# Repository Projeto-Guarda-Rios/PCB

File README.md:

# Guarda-Rios PCB Repository

This repository contains all PCB design files for the **Guarda-Rios Project** — an open-source, low-cost, low-power water quality monitoring system. Multiple stations are deployed along a river so that parameter spikes between adjacent stations reveal precisely where pollution enters the waterway.

The system has two PCBs:

| Board | Role | Placement |
|---|---|---|
| **AquaNode PCB** | Submerged sensor node — reads water parameters and transmits them over RS-485 | Below waterline |
| **Main PCB (PGR)** | Station hub — receives RS-485 data, manages power (solar + 18650 Li-ion), and sends data to the cloud via NB-IoT | Above waterline |

> GitHub organisation: [github.com/Projeto-Guarda-Rios](https://github.com/Projeto-Guarda-Rios)
> Project site: [guarda-rios.pt](https://guarda-rios.pt) · Data portal: [data.guarda-rios.pt](https://data.guarda-rios.pt)

---

## Directory Structure

```
PCB/
├── AquaNode - PCB/          # AquaNode submerged sensor node
├── PGR - PCB/               # Main Station PCB
├── Datasheets/              # Component datasheets
├── Resources/               # Logos, SVGs, and images (silkscreen assets)
└── LICENSE
```

---

## AquaNode - PCB

The AquaNode is the submerged node of each station. It is built around an **STM32L053R8** microcontroller (ultra-low-power) and integrates a DS18B20 water temperature sensor (1-Wire) and a DFRobot SEN0554 turbidity sensor. Readings are encoded into the custom Guarda-Rios protocol and transmitted to the Main PCB over RS-485.

```
AquaNode - PCB/
├── Renders/                              # PNG renders of the current board
│   ├── AquaNode - PCB.png               #   Top-side render
│   └── AquaNode - PCB - 2.png           #   Bottom-side / alternate angle render
│
├── AquaNode - PCB.step                  # STEP model of the assembled board
├── AquaNode - PCB - Render.step         # STEP model used for rendering
├── AquaNode - PCB.stl                   # STL mesh of the board
│
└── AquaNode - PCB/                      # KiCAD project (current version)
    ├── AquaNode - PCB.kicad_pro         #   KiCAD project file  ← open this in KiCAD
    ├── AquaNode - PCB.kicad_pcb         #   PCB layout
    ├── AquaNode - PCB.kicad_sch         #   Schematic
    ├── footprints/                      #   Custom footprint library
    ├── symbols/                         #   Custom symbol library
    └── production/                      # Production files (PCBA) — current version
        ├── -v2.0.zip                    #   Gerbers + drill files (upload to JLCPCB)
        ├── -v2.0_bom.csv               #   Bill of Materials
        ├── -v2.0_positions.csv         #   Component placement (pick & place)
        ├── -v2.0_designators.csv       #   Designator mapping
        ├── netlist.ipc                  #   IPC netlist
        └── backups/                     #   Auto-generated production backups
```

**Key files:**
- Edit the PCB: `AquaNode - PCB/AquaNode - PCB/AquaNode - PCB.kicad_pro`
- Order the board: `AquaNode - PCB/AquaNode - PCB/production/-v2.0.zip`
- BOM for assembly: `AquaNode - PCB/AquaNode - PCB/production/-v2.0_bom.csv`
- Positions for assembly: `AquaNode - PCB/AquaNode - PCB/production/-v2.0_positions.csv`

---

## PGR - PCB

The Main PCB (PGR) is the above-water hub of each station. It is built around an **ESP32-WROOM-32D** and includes an RS-485 receiver, NB-IoT modem, BMS (battery management system), 18650 Li-ion charger, and solar charger — making each station fully self-sufficient in the field.

```
PGR - PCB/
├── Renders/                              # PNG renders of the current board
│   ├── PGR.png                          #   Top-side render
│   └── PGR - 2.png                      #   Bottom-side / alternate angle render
│
├── PGR.step                             # STEP model of the assembled board
├── PGR-Solder.step                      # STEP model showing solder joints
├── PGR.3mf                             # 3MF model (for 3D printing / Fusion 360)
│
├── PGR - PCB - v1.0-v4.0.zip           # Archived KiCAD projects (versions 1.0 – 4.0)
├── PGR - PCB - v5.0.zip                # Archived KiCAD project (version 5.0)
│
├── gerbers/                             # Gerber archives for previous board versions
│   ├── PGR-gerbers-v1.0.zip
│   ├── PGR-gerbers-v2.0.zip
│   ├── PGR-gerbers-v3.0.zip
│   ├── PGR-gerbers-v3.1.zip
│   ├── PGR-gerbers-v4.0.zip
│   ├── PGR-gerbers.zip                  #   (legacy export)
│   ├── PGR-F_Paste.zip                  #   Front paste layer export
│   └── PGR-PTH.zip                      #   PTH drill file export
│
└── PGR - PCB/                           # KiCAD project (current version)
    ├── PGR.kicad_pro                    #   KiCAD project file  ← open this in KiCAD
    ├── PGR.kicad_pcb                    #   PCB layout
    ├── PGR.kicad_sch                    #   Schematic
    ├── PGR-Library.kicad_sym           #   Custom symbol library
    ├── PGR-FootPrints.pretty/          #   Custom footprint library
    ├── footprints/                      #   Additional footprints
    ├── symbols/                         #   Additional symbols
    └── production/                      # Production files (PCBA) — current versions
        ├── PGR_PCB_v5.1.zip            #   Gerbers + drill files — latest (upload to JLCPCB)
        ├── PGR_PCB_v5.1_bom.csv        #   Bill of Materials — latest
        ├── PGR_PCB_v5.1_positions.csv  #   Component placement — latest
        ├── PGR_PCB_v5.1_designators.csv
        ├── PGR_PCB_v5.0.zip            #   Gerbers + drill files — v5.0
        ├── PGR_PCB_v5.0_bom.csv        #   Bill of Materials — v5.0
        ├── PGR_PCB_v5.0_positions.csv
        ├── PGR_PCB_v5.0_designators.csv
        ├── bom-JLCPCB Assembly Order.xls  # JLCPCB-formatted BOM for online ordering
        ├── bom.csv
        ├── designators.csv
        ├── positions.csv
        ├── netlist.ipc
        └── backups/                    # Auto-generated production backups
```

**Key files:**
- Edit the PCB: `PGR - PCB/PGR - PCB/PGR.kicad_pro`
- Order the board (latest): `PGR - PCB/PGR - PCB/production/PGR_PCB_v5.1.zip`
- BOM for assembly (latest): `PGR - PCB/PGR - PCB/production/PGR_PCB_v5.1_bom.csv`
- Positions for assembly (latest): `PGR - PCB/PGR - PCB/production/PGR_PCB_v5.1_positions.csv`
- Previous version gerbers: `PGR - PCB/gerbers/`

> Note: There are no current production files inside `PGR - PCB/gerbers/` — that directory holds archives of older board revisions only. Current production files are inside `PGR - PCB/PGR - PCB/production/`.

---

## Datasheets

Reference datasheets for ICs and components used across both PCBs.

```
Datasheets/
├── STM32L053C6.PDF                       # AquaNode MCU — STM32L053 datasheet
├── an4467-getting-started-with-stm32l0xx-hardware-development-stmicroelectronics.pdf
│                                         # STM32L0 hardware development guide (ST AppNote AN4467)
└── st485eb.pdf                           # ST485EB RS-485 transceiver (used on AquaNode)
```

---

## Resources

Images, SVGs, and logos used in PCB silkscreen layers or project documentation.

```
Resources/
├── guarda_rios_logo.svg / .png          # Official Guarda-Rios project logo
├── dwtLogo.svg                          # Designer logo
├── MIT_license_logo.svg / .png         # MIT license badge
├── open_source_logo.svg                 # Open-source hardware logo
├── open-source-hardware6230.logowik.com.webp
├── logo-colegio-ribadouro.png           # School/institution logo
│
├── AquaNodeBack.svg                     # AquaNode back silkscreen artwork
├── AquaNodeBack - Sem Logo.svg          # AquaNode back silkscreen (no logo variant)
├── BackSilkScreen.svg                   # Generic back silkscreen asset
│
├── AquaNode_v2_image_top.png            # AquaNode v2 board image — top
├── AquaNode_v2_image_bottom.png         # AquaNode v2 board image — bottom
├── PGR_v5.1_image_top.png              # PGR v5.1 board image — top
├── PGR_v5.1_image_bottom.png           # PGR v5.1 board image — bottom
│
└── Gemini_Generated_Image_iya1lhiya1lhiya1.png   # AI-generated concept image
```

---

## Hardware Summary

| Parameter | AquaNode PCB | Main PCB (PGR) |
|---|---|---|
| MCU | STM32L053R8 | ESP32-WROOM-32D |
| Sensors | DS18B20 (temp), DFRobot SEN0554 (turbidity) | — |
| Communication | RS-485 out (custom protocol) | RS-485 in · NB-IoT out |
| Power | From Main PCB via RS-485 cable | Solar + 18650 Li-ion (BMS + charger on-board) |
| Placement | Submerged | Above waterline |
| CAD tool | KiCAD | KiCAD |

---

## License

This project is fully open-source. See [`LICENSE`](LICENSE) for details.

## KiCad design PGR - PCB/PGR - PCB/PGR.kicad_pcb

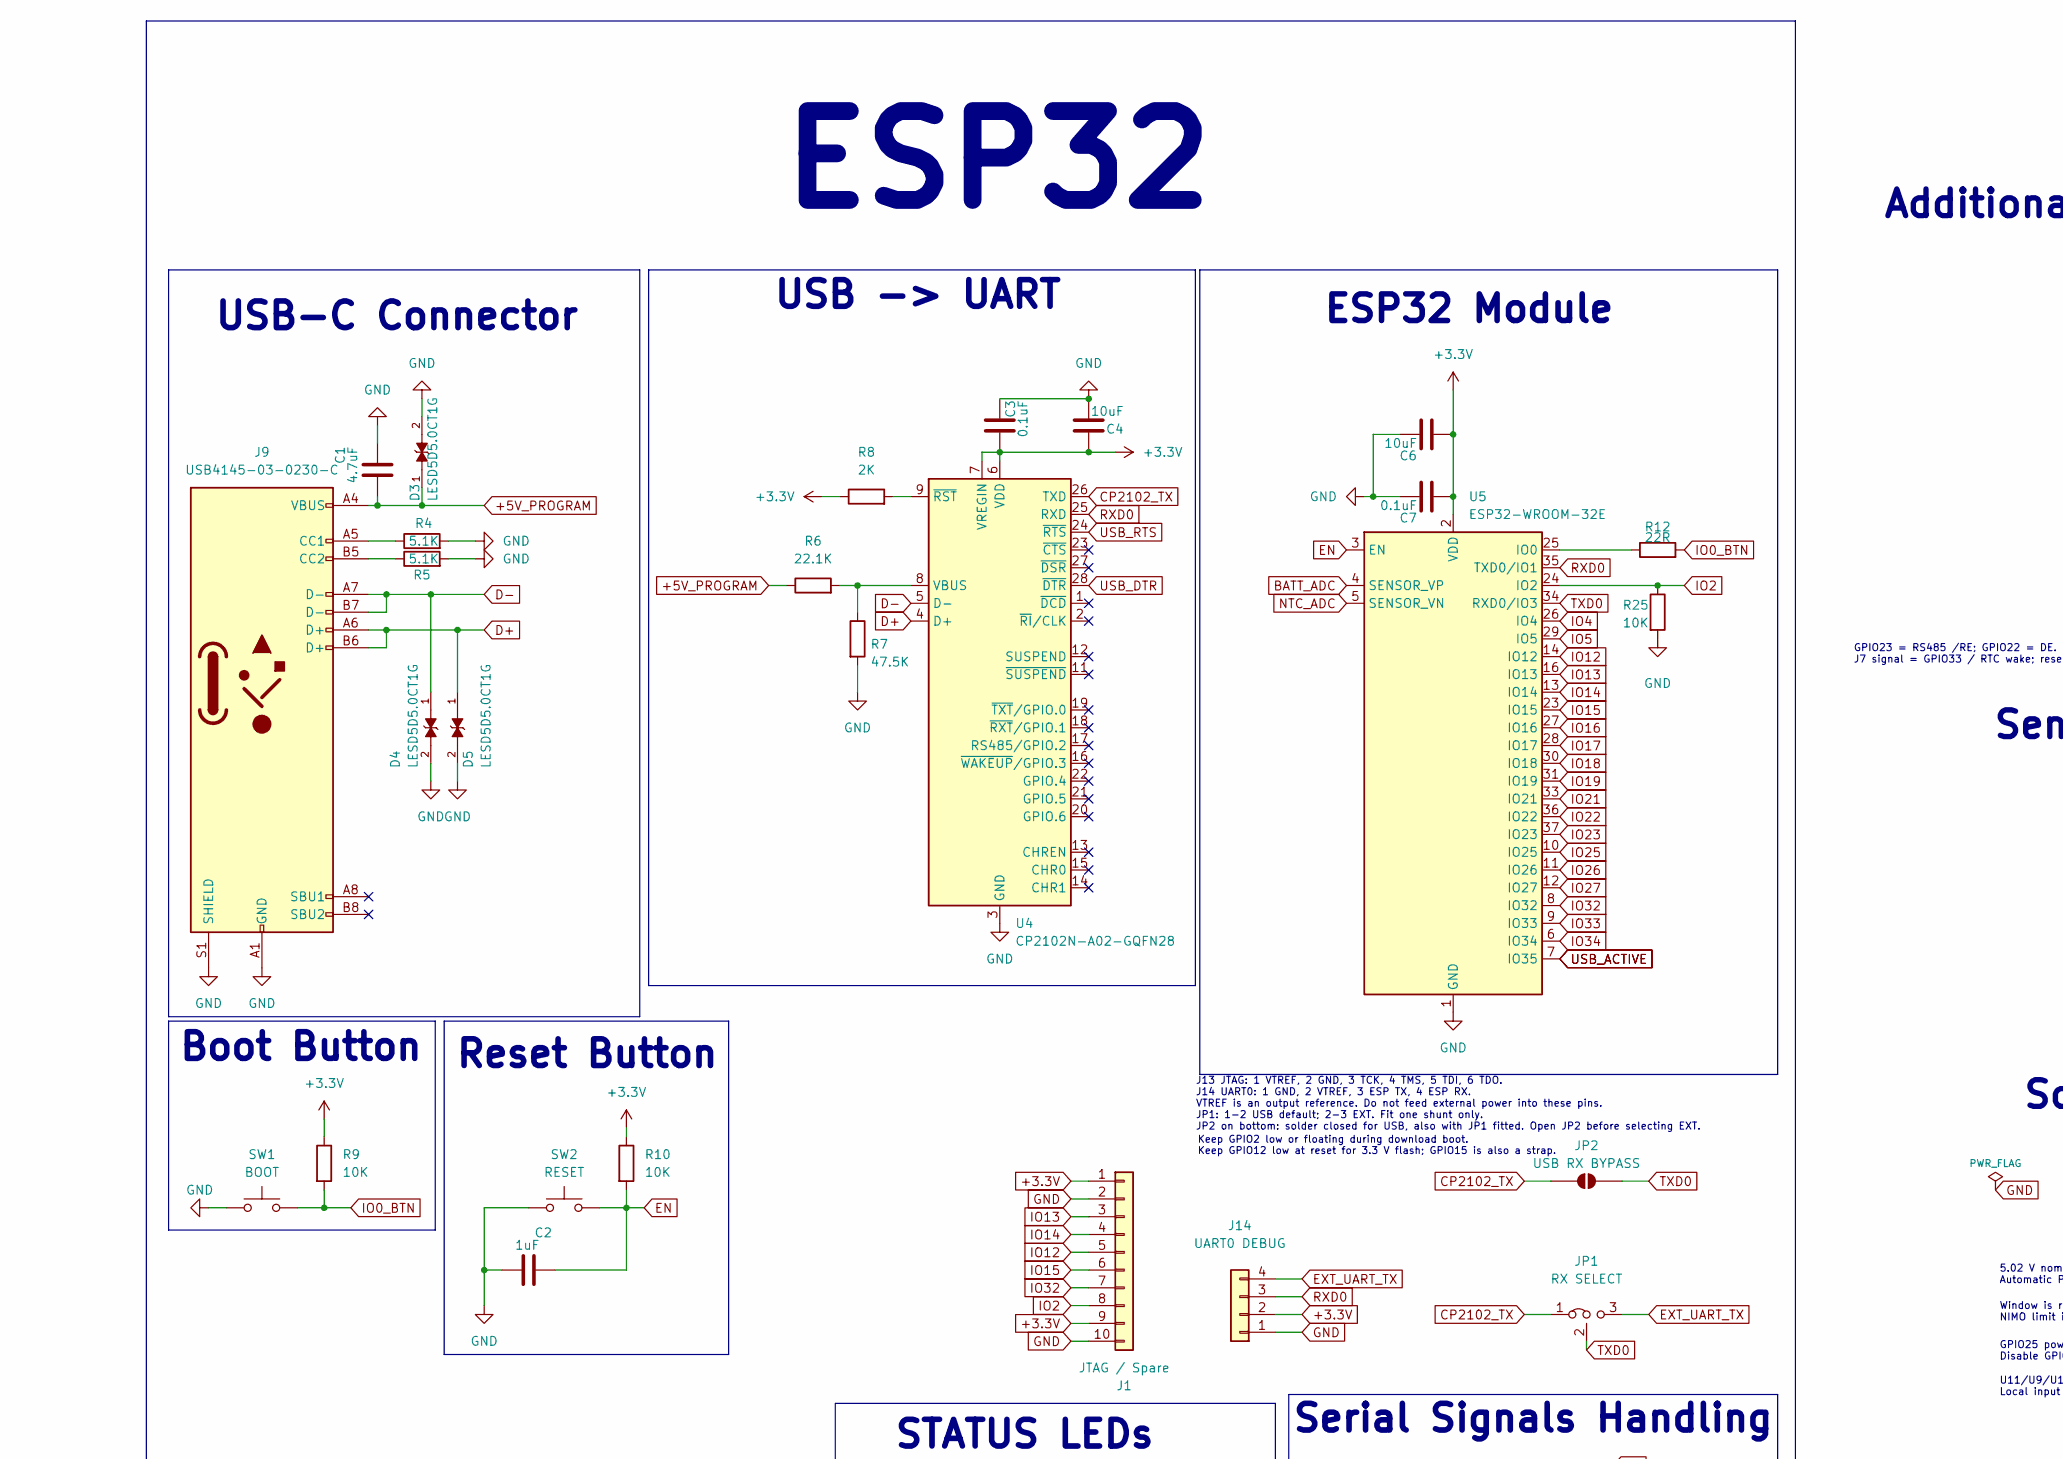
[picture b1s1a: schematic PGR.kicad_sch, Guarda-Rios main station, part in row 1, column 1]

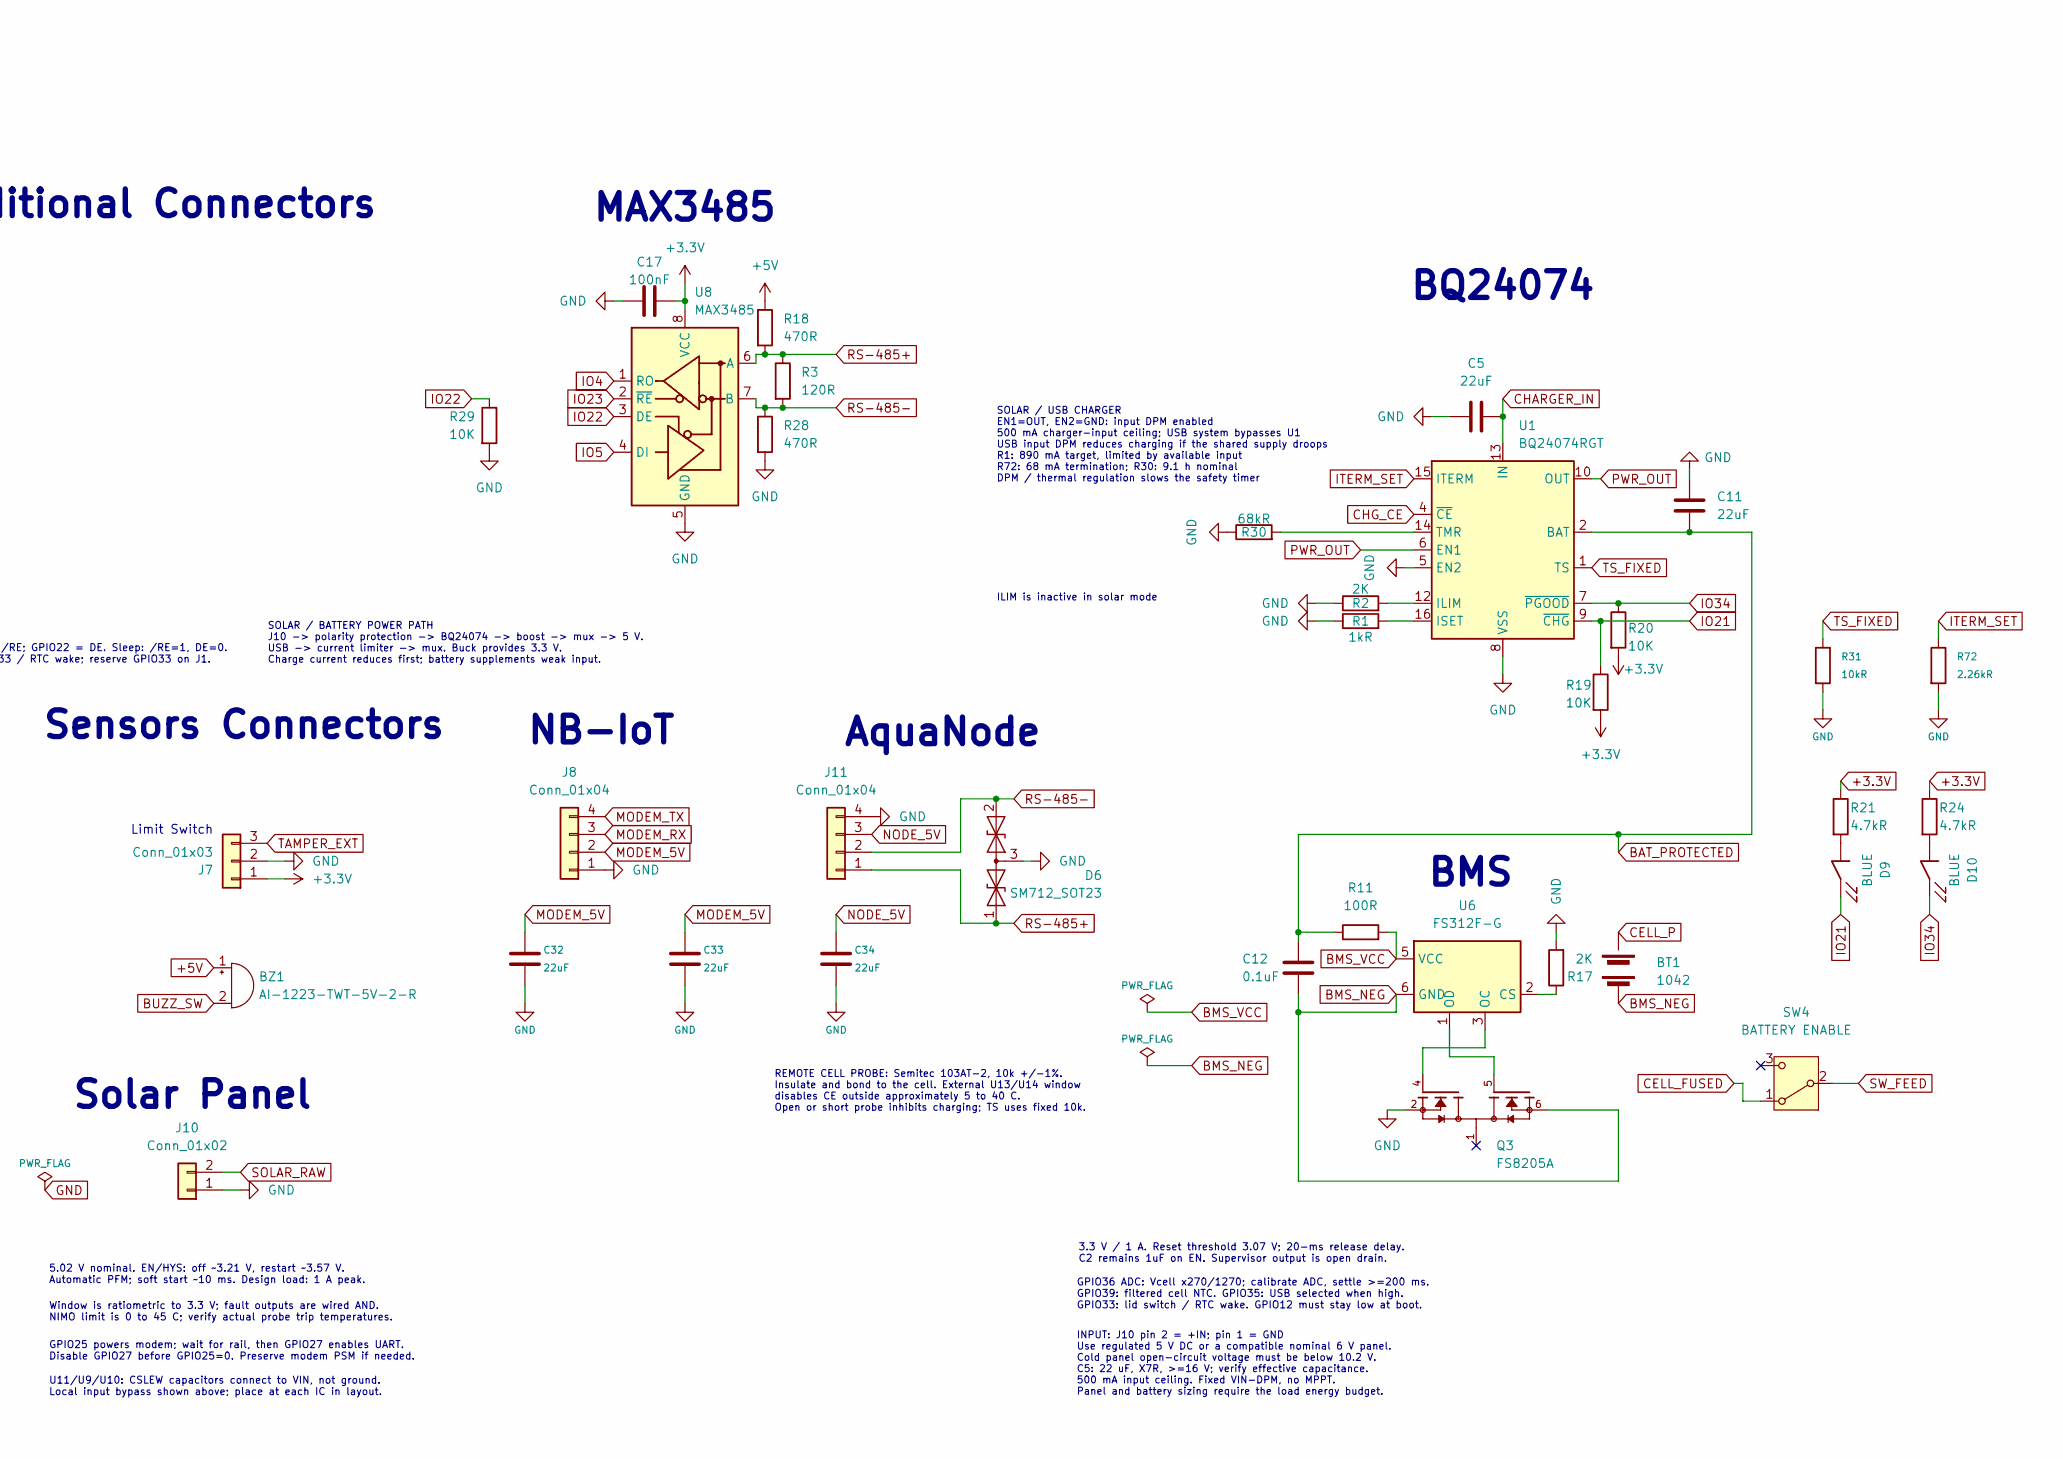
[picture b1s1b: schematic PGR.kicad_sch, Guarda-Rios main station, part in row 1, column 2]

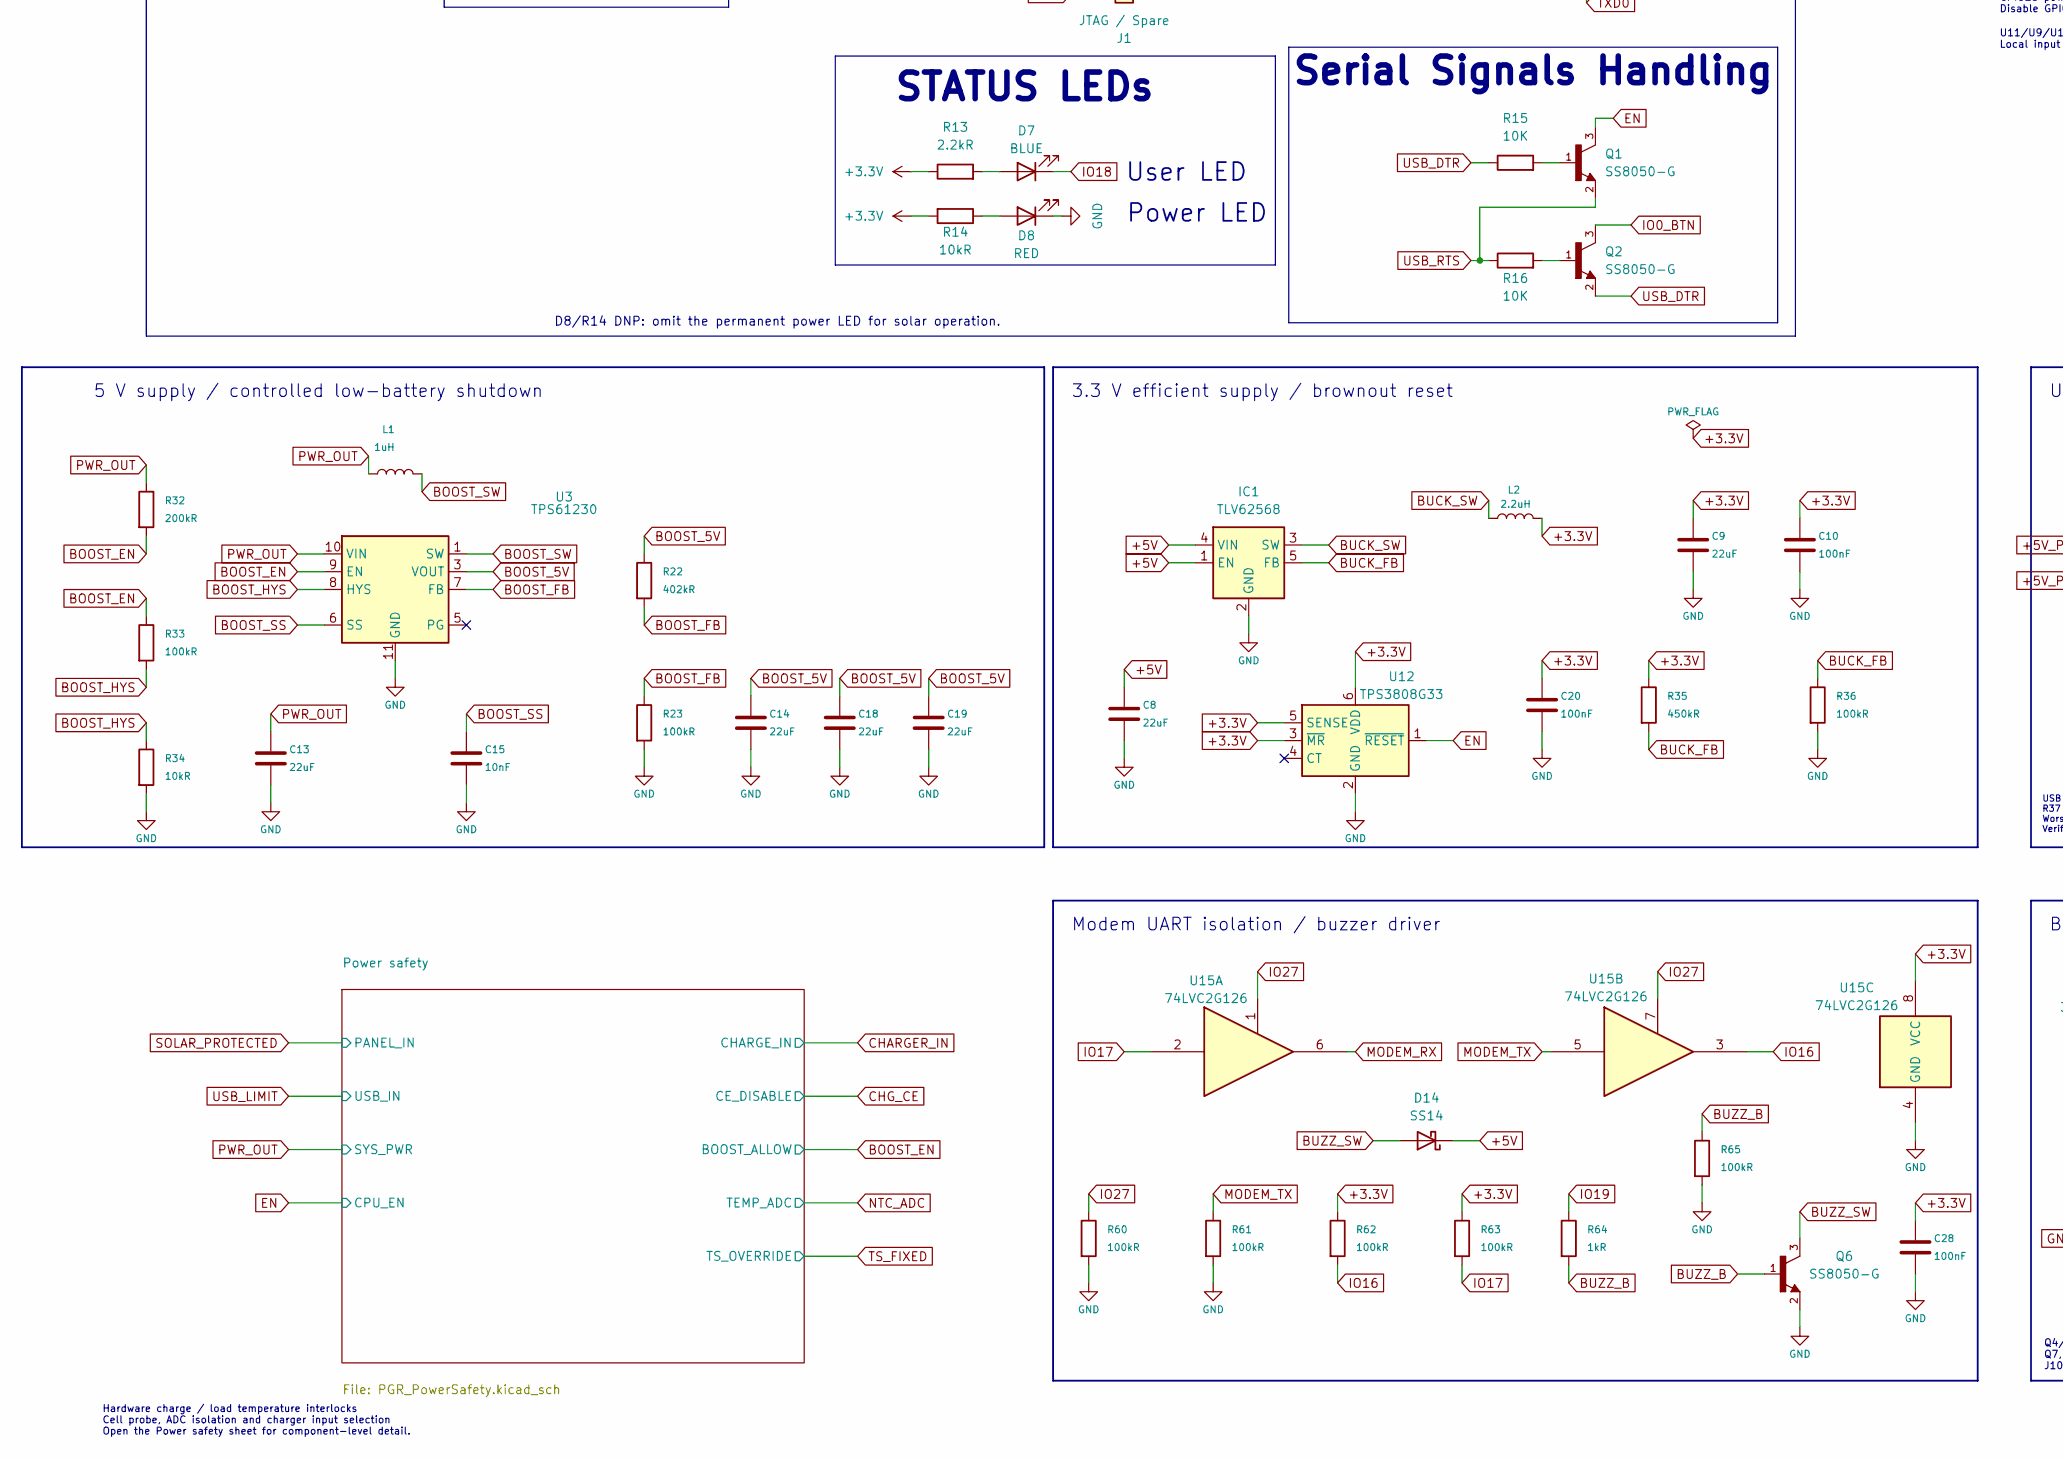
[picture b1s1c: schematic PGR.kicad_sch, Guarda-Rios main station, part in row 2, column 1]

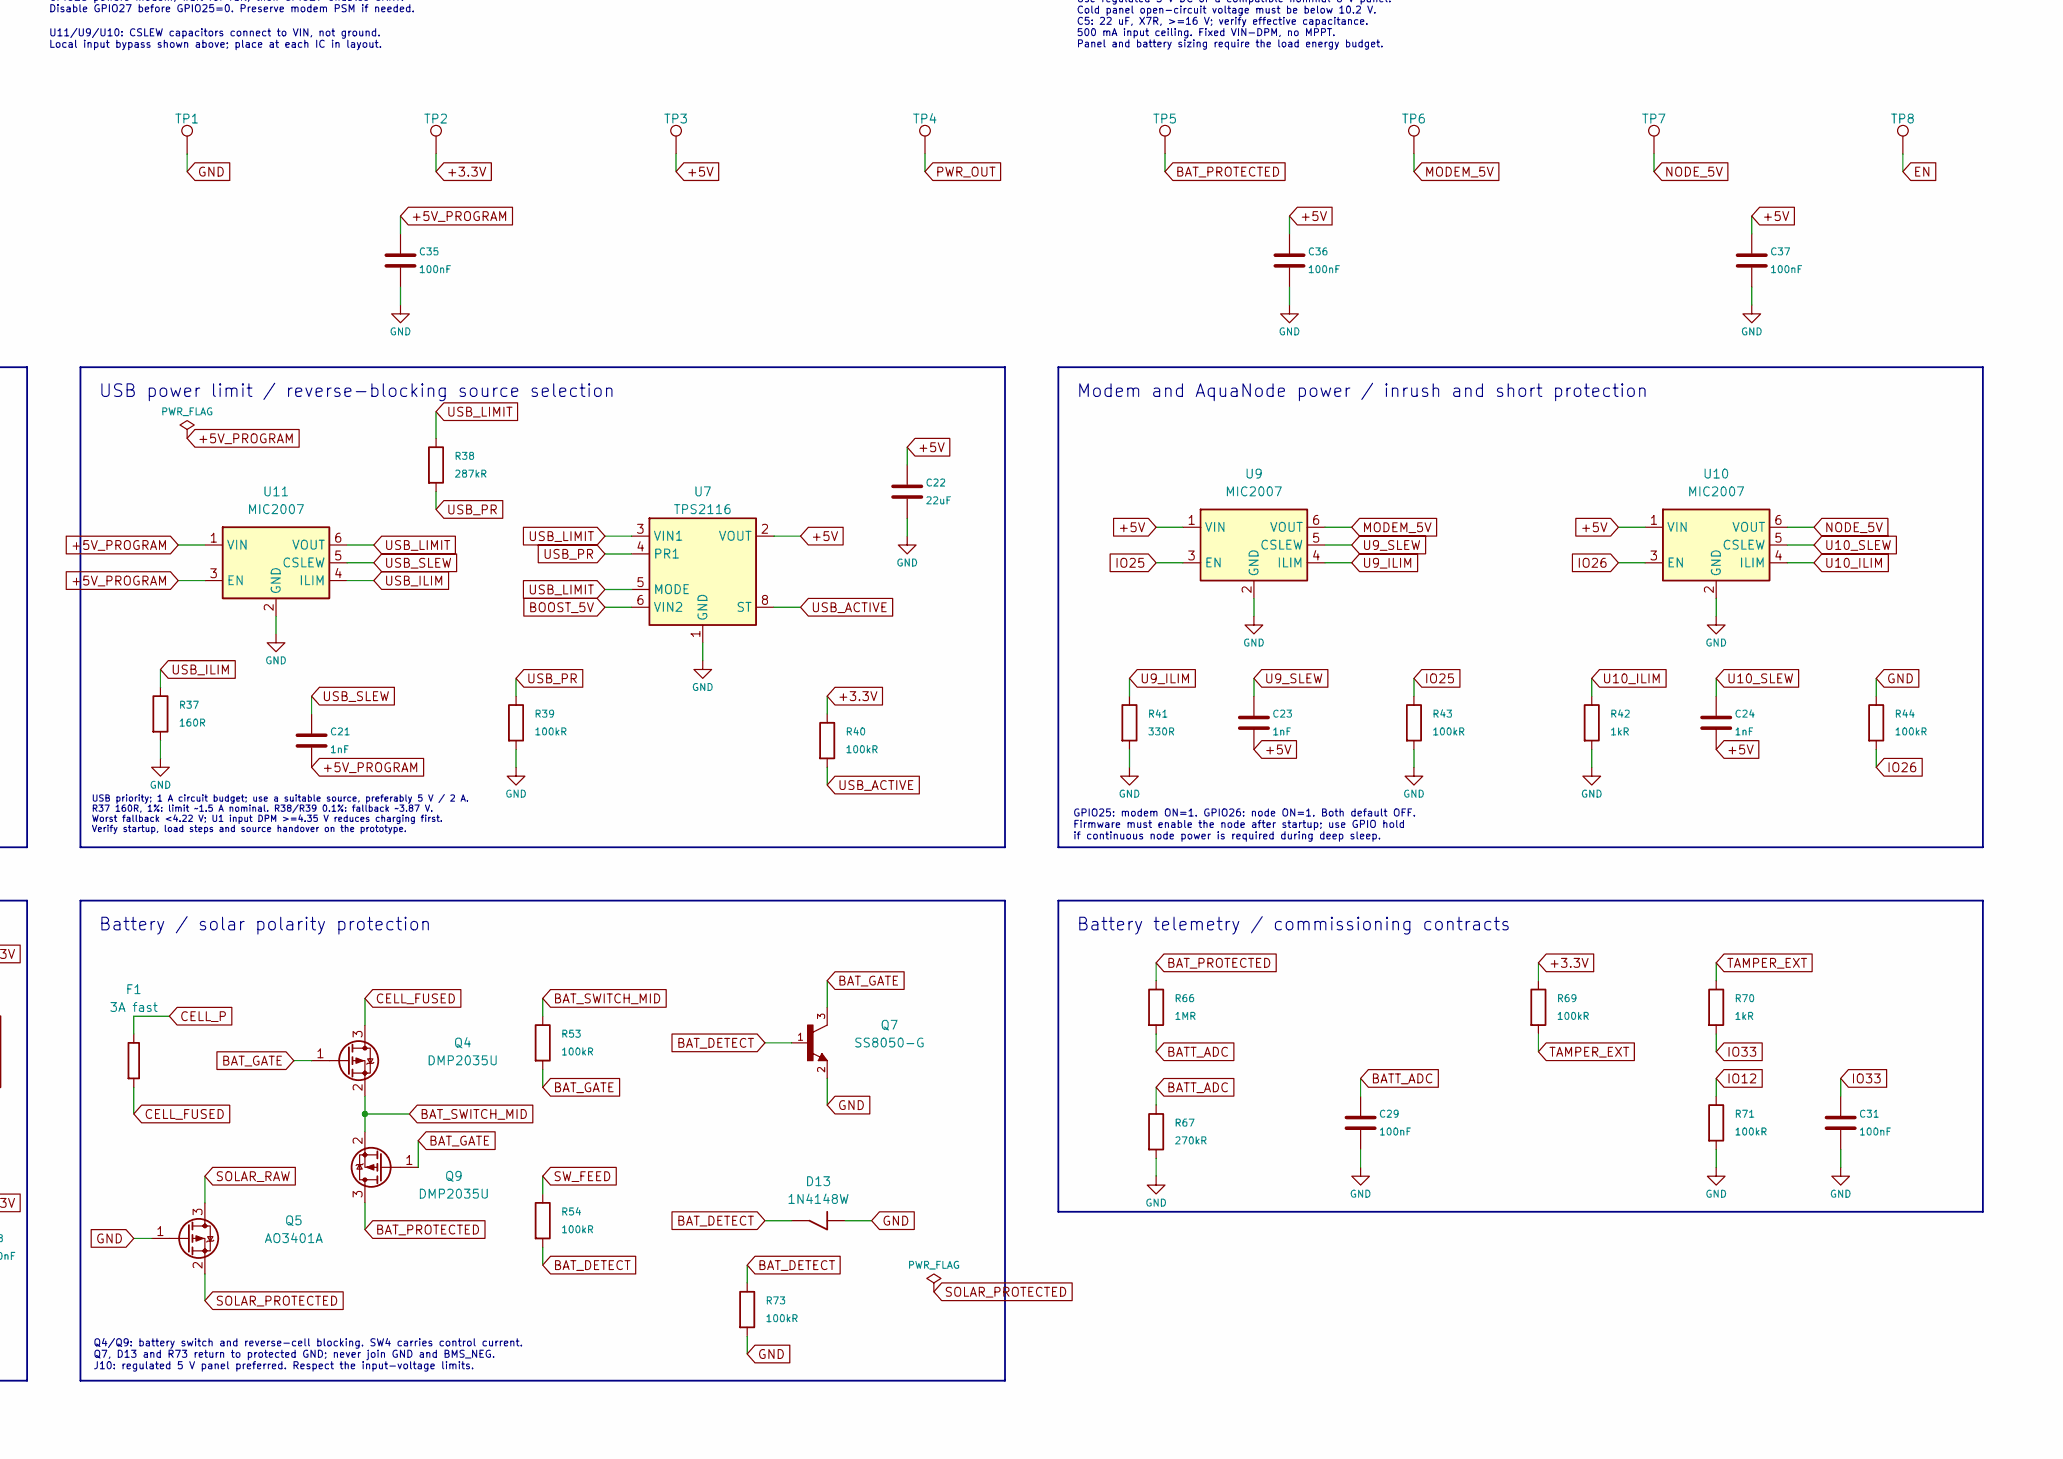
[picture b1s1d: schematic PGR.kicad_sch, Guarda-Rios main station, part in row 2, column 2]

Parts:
BT1: 1042; BatteryHolder_Keystone_1042_1x18650; MPN 1042; LCSC C5249310
BZ1: AI-1223-TWT-5V-2-R; Buzzer_12x9.5RM7.6; Rating 5V active magnetic indicator, 30mA max;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; MPN AI-1223-TWT-5V-2-R
C1: 4.7uF; C_0805_2012Metric; Rating >=10V X7R; effective >=1uF at 5V
C2: 1uF; C_0603_1608Metric
C3, C7, C12: 0.1uF; C_0603_1608Metric
C4, C6: 10uF; C_0805_2012Metric
C5, C11: 22uF; C_1210_3225Metric; Rating 16V X7R +/-20%; verify effective C >=4.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; MPN C3225X7R1C226M250AC
C8, C9, C13, C14, C18, C19, C22: 22uF; C_1210_3225Metric; Rating 22uF 16V X7R +/-20%; 1210; DC bias eval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; MPN C3225X7R1C226M250AC
C10, C17, C20, C28, C29, C31, C35, C36, C37: 100nF; C_0603_1608Metric
C15: 10nF; C_0603_1608Metric
C21, C23, C24: 1nF; C_0603_1608Metric
C32, C33, C34: 22uF; C_1210_3225Metric; Rating 16V X7R +/-20%; MPN C3225X7R1C226M250AC
D3, D4, D5: LESD5D5.0CT1G; TVS_LESD5D5.0CT1G; PARTREV O
D6: SM712_SOT23; SOT-23
D7: BLUE; LED_0603_1608Metric
D8: RED; LED_0603_1608Metric
D9: BLUE; LED_0603_1608Metric_PGR_D9
D10: BLUE; LED_0603_1608Metric_PGR_D10
D13: 1N4148W; D_SOD-123; MPN 1N4148W-7-F
D14: SS14; D_SMA; MPN SS14
F1: 3A fast; Fuse_Littelfuse-NANO2-451_453_PGR_F1; Rating 3A very fast; 300A breaking at 32VDC; MPN 0451003.MRL
IC1: TLV62568; SOT-23-5; MPN TLV62568DBVR
J1: JTAG / Spare; PinHeader_1x10_P2.54mm_Vertical
J7: Conn_01x03; JST_XH_B3B-XH-A_1x03_P2.50mm_Vertical
J8: Conn_01x04; JST_XH_B4B-XH-A_1x04_P2.50mm_Vertical
J9: USB4145-03-0230-C; USB_C_GCT_USB4145_03_0230_C_Vertical; MPN USB4145-03-0230-C; LCSC C5291559
J10: Conn_01x02; JST_XH_B2B-XH-A_1x02_P2.50mm_Vertical
J11: Conn_01x04; JST_XH_B4B-XH-A_1x04_P2.50mm_Vertical_PGR_J11
J14: UART0 DEBUG; PinHeader_1x04_P2.54mm_Vertical
JP1: RX SELECT; PinHeader_1x03_P2.54mm_Vertical; MPN M20-9990345
JP2: USB RX BYPASS; SolderJumper-2_P1.3mm_Open_Pad1.0x1.5mm
L1: 1uH; L_Coilcraft_XAL4020-XXX; MPN XAL4020-102MEC
L2: 2.2uH; L_Coilcraft_XAL4020-XXX; MPN XAL4020-222MEC
Q1: SS8050-G; TRANS_SS8050-G_PGR_Q1; PARTREV A
Q2: SS8050-G; TRANS_SS8050-G_PGR_Q2; PARTREV A
Q3: FS8205A; SOP65P640X120-8N; PARTREV 1.7
Q4, Q9: DMP2035U; SOT-23; MPN DMP2035U-7
Q5: AO3401A; SOT-23; MPN AO3401A
Q6, Q7: SS8050-G; TRANS_SS8050-G; PARTREV A
R1, R42, R64, R70: 1kR; R_0603_1608Metric
R2, R8, R17: 2K; R_0603_1608Metric
R3: 120R; R_0603_1608Metric
R4, R5: 5.1K; R_0603_1608Metric
R6: 22.1K; R_0603_1608Metric
R7: 47.5K; R_0603_1608Metric
R9, R10, R15, R16, R19, R20, R25, R29: 10K; R_0603_1608Metric
R11: 100R; R_0603_1608Metric
R12: 22R; R_0603_1608Metric
R13: 2.2kR; R_0603_1608Metric
R14, R31: 10kR; R_0603_1608Metric
R18, R28: 470R; R_0603_1608Metric; Tolerance 1%
R21, R24: 4.7kR; R_0603_1608Metric
R22: 402kR; R_0603_1608Metric; Tolerance 0.1%; MPN RT0603BRD07402KL
R23: 100kR; R_0603_1608Metric; Tolerance 0.1%; MPN RT0603BRD07100KL
R30: 68kR; R_0603_1608Metric
R32: 200kR; R_0603_1608Metric; Tolerance 0.1%
R33, R36, R39: 100kR; R_0603_1608Metric; Tolerance 0.1%
R34: 10kR; R_0603_1608Metric; Tolerance 0.1%
R35: 450kR; R_0603_1608Metric; Tolerance 0.1%
R37: 160R; R_0603_1608Metric; Tolerance 1%
R38: 287kR; R_0603_1608Metric; Tolerance 0.1%
R40, R43, R44, R53, R54, R60, R61, R62, R63, R65, R69, R71: 100kR; R_0603_1608Metric
R41: 330R; R_0603_1608Metric
R66: 1MR; R_0603_1608Metric; Tolerance 0.1%
R67: 270kR; R_0603_1608Metric; Tolerance 0.1%
R72: 2.26kR; R_0603_1608Metric; Tolerance 1%
R73: 100kR; R_0603_1608Metric; Tolerance 1%; MPN RC0603FR-07100KL
SW1: BOOT; SW_Push_SPST_NO_Alps_SKRK; MPN SKRKAHE020; LCSC C202388
SW2: RESET; SW_Push_SPST_NO_Alps_SKRK; MPN SKRKAHE020; LCSC C202388
SW4: BATTERY ENABLE; SW_Slide_CK_1101M2S3CBE2; Rating Gold low-level/dry-circuit contacts, 0.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; MPN 1101M2S3CBE2; LCSC C2798505
TP1, TP2, TP3, TP4, TP5, TP6, TP8: TP; TestPoint_Pad_D1.0mm
TP7: TP; TestPoint_Pad_D1.0mm_PGR_TP7
U1: BQ24074RGT; VQFN-16-1EP_3x3mm_P0.5mm_EP1.6x1.6mm_PGR_U1
U3: TPS61230; Texas_S-PVSON-N10_ThermalVias_PGR_U3; MPN TPS61230DRCR
U4: CP2102N-A02-GQFN28; QFN-28-1EP_5x5mm_P0.5mm_EP3.35x3.35mm_PGR_U4
U5: ESP32-WROOM-32E; ESP32-WROOM-32D_PGR_U5
U6: FS312F-G; SOT-23-6; MPN FS312F-G; LCSC C82736
U7: TPS2116; SOT-583-8_PGR_U7; MPN TPS2116DRLR
U8: MAX3485; SOIC-8_3.9x4.9mm_P1.27mm
U9, U10, U11: MIC2007; SOT-23-6; MPN MIC2007YM6-TR
U12: TPS3808G33; SOT-23-6; MPN TPS3808G33DBVR
U15: 74LVC2G126; VSSOP-8_2.3x2mm_P0.5mm; MPN SN74LVC2G126DCUR

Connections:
+3.3V: C3.2, C4.2, C6.2, C7.2, C9.1, C10.1, C17.2, C20.1, C28.1, J1.1, J1.9, J7.1, J14.2, L2.2, R8.1, R9.1, R10.1, R13.1, R14.2, R19.2, R20.2, R21.1, R24.1, R35.1, R40.1, R62.1, R63.1, R69.1, TP2.1 (1_1), U4.6 (VDD), U4.7 (VREGIN), U5.2 (VDD), U8.8 (VCC), U12.3 (~MR), U12.5 (SENSE), U12.6 (VDD), U15.8 (VCC)
+5V: BZ1.1 (+), C8.1, C22.1, C23.2, C24.2, C36.1, C37.1, D14.1 (K), IC1.1 (EN), IC1.4 (VIN), R18.1, TP3.1 (1_1), U7.2 (VOUT), U7.7 (VOUT), U9.1 (VIN), U10.1 (VIN)
+5V_PROGRAM: C1.2, C21.2, C35.1, D3.1, J9.A4 (VBUS), J9.A9 (VBUS), J9.B4 (VBUS), J9.B9 (VBUS), R6.1, U11.1 (VIN), U11.3 (EN)
BATT_ADC: C29.1, R66.2, R67.1, U5.4 (SENSOR_VP)
BAT_DETECT: D13.1 (K), Q7.1, R54.2, R73.1
BAT_GATE: Q4.1 (G), Q7.3, Q9.1 (G), R53.2
BAT_PROTECTED: C11.2, C12.1, Q9.3 (D), R11.1, R66.1, TP5.1 (1_1), U1.2 (BAT), U1.3 (BAT)
BAT_SWITCH_MID: Q4.2 (S), Q9.2 (S), R53.1
BMS_NEG: BT1.2 (-), C12.2, Q3.6, Q3.7, U6.6 (GND)
BMS_VCC: R11.2, U6.5 (VCC)
BOOST_5V: C14.1, C18.1, C19.1, R22.1, U3.3 (VOUT), U3.4 (VOUT), U7.6 (VIN2)
BOOST_EN: R32.2, R33.1, U3.9 (EN); also elsewhere on the board
BOOST_FB: R22.2, R23.1, U3.7 (FB)
BOOST_HYS: R33.2, R34.1, U3.8 (HYS)
BOOST_SS: C15.1, U3.6 (SS)
BOOST_SW: L1.2, U3.1 (SW), U3.2 (SW)
BUCK_FB: IC1.5 (FB), R35.2, R36.1
BUCK_SW: IC1.3 (SW), L2.1
BUZZ_B: Q6.1, R64.2, R65.1
BUZZ_SW: BZ1.2 (-), D14.2 (A), Q6.3
CELL_FUSED: F1.2, Q4.3 (D), SW4.1 (A)
CELL_P: BT1.1 (+), F1.1
CHARGER_IN: C5.2, U1.13 (IN); also elsewhere on the board
CHG_CE: U1.4 (~CE); also elsewhere on the board
CP2102_TX: JP1.1 (A), JP2.1 (A), U4.26 (TXD)
D+: D5.1, J9.A6 (D+), J9.B6 (D+), U4.4 (D+)
D-: D4.1, J9.A7 (D-), J9.B7 (D-), U4.5 (D-)
EN: C2.1, Q1.3, R10.2, SW2.2, TP8.1 (1_1), U5.3 (EN), U12.1 (~RESET); also elsewhere on the board
EXT_UART_TX: J14.4, JP1.3 (B)
GND: C1.1, C2.2, C3.1, C4.1, C5.1, C6.1, C7.1, C8.2, C9.2, C10.2, C11.1, C13.2, C14.2, C15.2, C17.1, C18.2, C19.2, C20.2, C22.2, C28.2, C29.2, C31.2, C32.2, C33.2, C34.2, C35.2, C36.2, C37.2, D3.2, D4.2, D5.2, D6.3 (common), D8.1 (K), D13.2 (A), IC1.2 (GND), J1.2, J1.10, J7.2, J8.1, J9.A1 (GND), J9.A12 (GND), J9.B1 (GND), J9.B12 (GND), J9.S1 (SHIELD), J10.1, J11.4, J14.1, Q3.2, Q3.3, Q5.1 (G), Q6.2, Q7.2, R1.1, R2.1, R4.2, R5.2, R7.2, R17.2, R23.2, R25.2, R28.2, R29.2, R30.1, R31.2, R34.2, R36.2, R37.2, R39.2, R41.2, R42.2, R43.2, R44.1, R60.2, R61.2, R65.2, R67.2, R71.2, R72.2, R73.2, SW1.1, SW2.1, TP1.1 (1_1), U1.5 (EN2), U1.8 (VSS), U1.17 (VSS), U3.11 (GND), U4.3 (GND), U4.29 (GND), U5.1 (GND), U5.15 (GND), U5.38 (GND), U5.39 (GND), U7.1 (GND), U8.5 (GND), U9.2 (GND), U10.2 (GND), U11.2 (GND), U12.2 (GND), U15.4 (GND); also elsewhere on the board
IO0_BTN: Q2.3, R9.2, R12.2, SW1.2
IO2: J1.8, R25.1, U5.24 (IO2)
IO4: U5.26 (IO4), U8.1 (RO)
IO5: U5.29 (IO5), U8.4 (DI)
IO12: J1.5, R71.1, U5.14 (IO12)
IO13: J1.3, U5.16 (IO13)
IO14: J1.4, U5.13 (IO14)
IO15: J1.6, U5.23 (IO15)
IO16: R62.2, U5.27 (IO16), U15.3
IO17: R63.2, U5.28 (IO17), U15.2
IO18: D7.1 (K), U5.30 (IO18)
IO19: R64.1, U5.31 (IO19)
IO21: D9.1 (K), R19.1, U1.9 (~CHG), U5.33 (IO21)
IO22: R29.1, U5.36 (IO22), U8.3 (DE)
IO23: U5.37 (IO23), U8.2 (~RE)
IO25: R43.1, U5.10 (IO25), U9.3 (EN)
IO26: R44.2, U5.11 (IO26), U10.3 (EN)
IO27: R60.1, U5.12 (IO27), U15.1, U15.7
IO32: J1.7, U5.8 (IO32)
IO33: C31.1, R70.2, U5.9 (IO33)
IO34: D10.1 (K), R20.1, U1.7 (~PGOOD), U5.6 (IO34)
ITERM_SET: R72.1, U1.15 (ITERM)
MODEM_5V: C32.1, C33.1, J8.2, TP6.1 (1_1), U9.6 (VOUT)
MODEM_RX: J8.3, U15.6
MODEM_TX: J8.4, R61.1, U15.5
NODE_5V: C34.1, J11.3, TP7.1 (1_1), U10.6 (VOUT)
NTC_ADC: U5.5 (SENSOR_VN); also elsewhere on the board
unnamed: D7.2 (A), R13.2
unnamed: D8.2 (A), R14.1
unnamed: D9.2 (A), R21.2
unnamed: D10.2 (A), R24.2
unnamed: J9.A5 (CC1), R4.1
unnamed: J9.B5 (CC2), R5.1
unnamed: Q1.1, R15.2
unnamed: Q2.1, R16.2
unnamed: R2.2, U1.12 (ILIM)
unnamed: R1.2, U1.16 (ISET)
unnamed: R30.2, U1.14 (TMR)
unnamed: R6.2, R7.1, U4.8 (VBUS)
unnamed: R8.2, U4.9 (~RST)
unnamed: R12.1, U5.25 (IO0)
unnamed: R17.1, U6.2 (CS)
unnamed: Q3.4, U6.3 (OC)
unnamed: Q3.5, U6.1 (OD)
PWR_OUT: C13.1, L1.1, R32.1, TP4.1 (1_1), U1.6 (EN1), U1.10 (OUT), U1.11 (OUT), U3.10 (VIN); also elsewhere on the board
RS-485+: D6.1 (A1), J11.1, R3.1, R18.2, U8.6 (A)
RS-485-: D6.2 (A2), J11.2, R3.2, R28.1, U8.7 (B)
RXD0: J14.3, U4.25 (RXD), U5.35 (TXD0/IO1)
SOLAR_PROTECTED: Q5.2 (S); also elsewhere on the board
SOLAR_RAW: J10.2, Q5.3 (D)
SW_FEED: R54.1, SW4.2 (B)
TAMPER_EXT: J7.3, R69.2, R70.1
TS_FIXED: R31.1, U1.1 (TS); also elsewhere on the board
TXD0: JP1.2 (C), JP2.2 (B), U5.34 (RXD0/IO3)
U9_ILIM: R41.1, U9.4 (ILIM)
U9_SLEW: C23.1, U9.5 (CSLEW)
U10_ILIM: R42.1, U10.4 (ILIM)
U10_SLEW: C24.1, U10.5 (CSLEW)
USB_ACTIVE: R40.2, U5.7 (IO35), U7.8 (ST)
USB_DTR: Q2.2, R15.1, U4.28 (~DTR)
USB_ILIM: R37.1, U11.4 (ILIM)
USB_LIMIT: R38.1, U7.3 (VIN1), U7.5 (MODE), U11.6 (VOUT); also elsewhere on the board
USB_PR: R38.2, R39.1, U7.4 (PR1)
USB_RTS: Q1.2, R16.1, U4.24 (~RTS)
USB_SLEW: C21.1, U11.5 (CSLEW)

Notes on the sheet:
REMOTE CELL PROBE: Semitec 103AT-2, 10k +/-1%. Insulate and bond to the cell. External U13/U14 window disables CE outside approximately 5 to 40 C. Open or short probe inhibits charging; TS uses fixed 10k.
GPIO36 ADC: Vcell x270/1270; calibrate ADC, settle >=200 ms. GPIO39: filtered cell NTC. GPIO35: USB selected when high. GPIO33: lid switch / RTC wake. GPIO12 must stay low at boot.
Window is ratiometric to 3.3 V; fault outputs are wired AND. NIMO limit is 0 to 45 C; verify actual probe trip temperatures.
Sensors Connectors
STATUS LEDs
MAX3485
NB-IoT
ESP32 Module
INPUT: J10 pin 2 = +IN; pin 1 = GND Use regulated 5 V DC or a compatible nominal 6 V panel. Cold panel open-circuit voltage must be below 10.2 V. C5: 22 uF, X7R, >=16 V; verify effective capacitance. 500 mA input ceiling. Fixed VIN-DPM, no MPPT. Panel and battery sizing require the load energy budg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
Limit Switch
Battery telemetry / commissioning contracts
GPIO23 = RS485 /RE; GPIO22 = DE. Sleep: /RE=1, DE=0. J7 signal = GPIO33 / RTC wake; reserve GPIO33 on J1.
USB power limit / reverse-blocking source selection
3.3 V / 1 A. Reset threshold 3.07 V; 20-ms release delay. C2 remains 1uF on EN. Supervisor output is open drain.
3.3 V efficient supply / brownout reset
5.02 V nominal. EN/HYS: off ~3.21 V, restart ~3.57 V. Automatic PFM; soft start ~10 ms. Design load: 1 A peak.
Keep GPIO2 low or floating during download boot. Keep GPIO12 low at reset for 3.3 V flash; GPIO15 is also a strap.
ILIM is inactive in solar mode
ESP32
SOLAR / BATTERY POWER PATH J10 -> polarity protection -> BQ24074 -> boost -> mux -> 5 V. USB -> current limiter -> mux. Buck provides 3.3 V. Charge current reduces first; battery supplements weak input.
Additional Connectors
GPIO25 powers modem; wait for rail, then GPIO27 enables UART. Disable GPIO27 before GPIO25=0. Preserve modem PSM if needed.
GPIO25: modem ON=1. GPIO26: node ON=1. Both default OFF. Firmware must enable the node after startup; use GPIO hold if continuous node power is required during deep sleep.
Modem and AquaNode power / inrush and short protection
J13 JTAG: 1 VTREF, 2 GND, 3 TCK, 4 TMS, 5 TDI, 6 TDO. J14 UART0: 1 GND, 2 VTREF, 3 ESP TX, 4 ESP RX. VTREF is an output reference. Do not feed external power into these pins. JP1: 1-2 USB default; 2-3 EXT. Fit one shunt only. JP2 on bottom: solder closed for USB, also with JP1 fitted. Open JP2 befo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
User LED
BMS
Solar Panel
BQ24074
U11/U9/U10: CSLEW capacitors connect to VIN, not ground. Local input bypass shown above; place at each IC in layout.
USB -> UART
Hardware charge / load temperature interlocks Cell probe, ADC isolation and charger input selection Open the Power safety sheet for component-level detail.
Boot Button
D8/R14 DNP: omit the permanent power LED for solar operation.
Power LED
USB priority; 1 A circuit budget; use a suitable source, preferably 5 V / 2 A. R37 160R, 1%: limit ~1.5 A nominal. R38/R39 0.1%: fallback ~3.87 V. Worst fallback <4.22 V; U1 input DPM >=4.35 V reduces charging first. Verify startup, load steps and source handover on the prototype.
Q4/Q9: battery switch and reverse-cell blocking. SW4 carries control current. Q7, D13 and R73 return to protected GND; never join GND and BMS_NEG. J10: regulated 5 V panel preferred. Respect the input-voltage limits.
USB-C Connector
Reset Button
Modem UART isolation / buzzer driver
